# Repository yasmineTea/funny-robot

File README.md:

<h1>The Funny Exercise Robot</h1>

yo watup nino

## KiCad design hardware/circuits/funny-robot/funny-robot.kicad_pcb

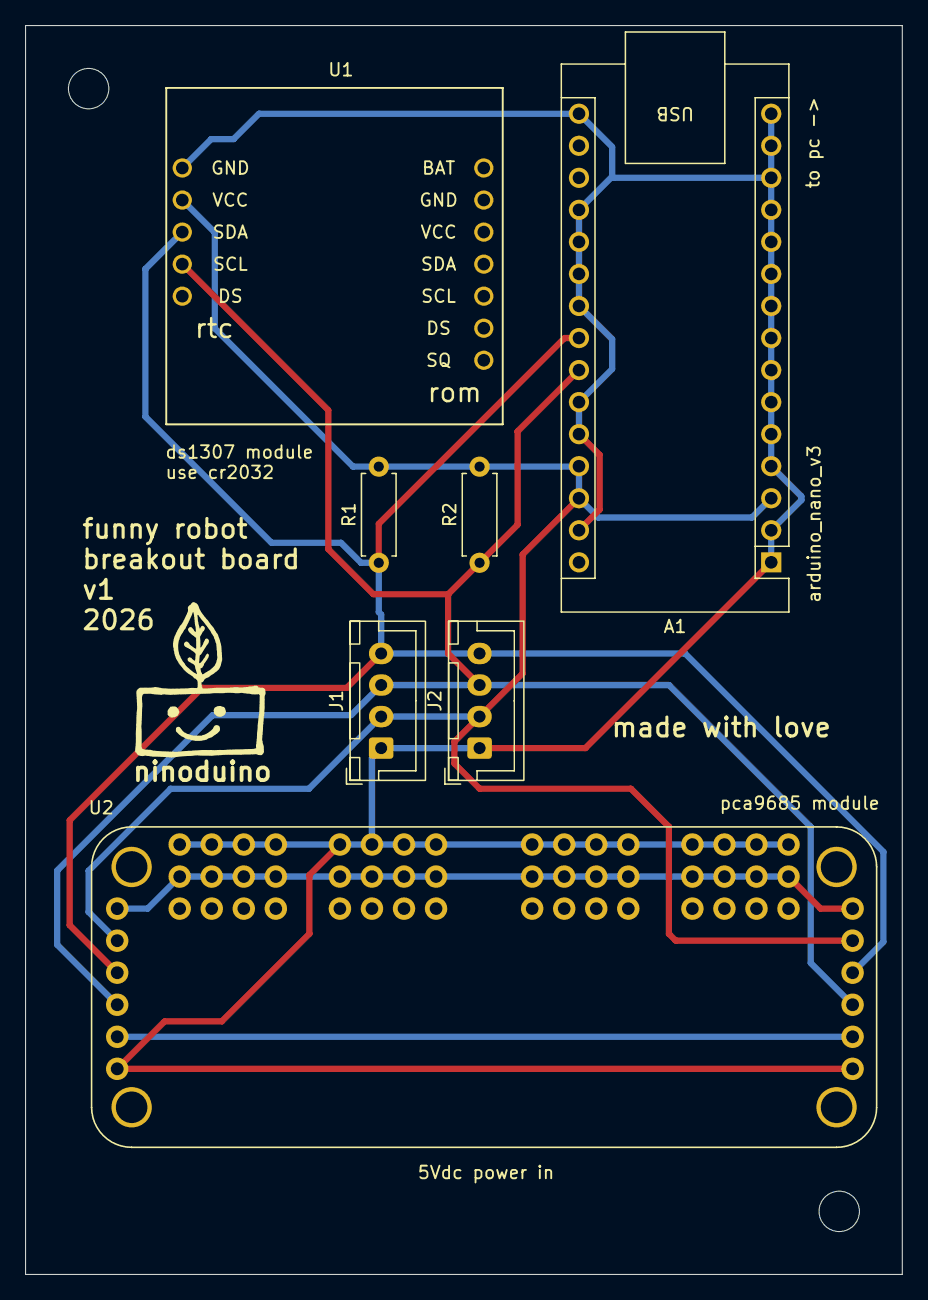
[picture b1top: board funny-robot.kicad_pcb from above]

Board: 2 copper layers, 69.5 x 99.0 mm, 7 parts (0 on the bottom side), 6 nets.

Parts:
A1: arduino_nano_v3; Arduino_Nano
J1: To SSD1306OLED; JST_XH_B4B-XH-A_1x04_P2.50mm_Vertical
J2: I2C Jumper; JST_XH_B4B-XH-A_1x04_P2.50mm_Vertical
R1, R2: 10k; R_Axial_DIN0207_L6.3mm_D2.5mm_P7.62mm_Horizontal
U1: Tiny_RTC_DS1307
U2: pca9685 module; MODULE_815

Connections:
+5V: U2.V+_1 (V+), U2.V+_2 (V+), U2.V+_3 (V+), U2.V+_4 (V+), U2.V+_5 (V+), U2.V+_6 (V+), U2.V+_7 (V+), U2.V+_8 (V+), U2.V+_9 (V+), U2.V+_10 (V+), U2.V+_11 (V+), U2.V+_12 (V+), U2.V+_13 (V+), U2.V+_14 (V+), U2.V+_15 (V+), U2.V+_16 (V+), U2.V+_17 (V+), U2.V+_18 (V+)
GND: A1.1 (D1/TX), A1.2 (D0/RX), A1.4 (GND), A1.5 (D2), A1.6 (D3), A1.7 (D4), A1.8 (D5), A1.9 (D6), A1.10 (D7), A1.11 (D8), A1.12 (D9), A1.13 (D10), A1.14 (D11), A1.15 (D12), A1.16 (D13), A1.19 (A0), A1.20 (A1), A1.21 (A2), A1.22 (A3), A1.25 (A6), A1.26 (A7), A1.29 (GND), J1.1, J2.1, U1.8 (GND), U2.GND_1 (GND), U2.GND_2 (GND), U2.GND_3 (GND), U2.GND_4 (GND), U2.GND_5 (GND), U2.GND_6 (GND), U2.GND_7 (GND), U2.GND_8 (GND), U2.GND_9 (GND), U2.GND_10 (GND), U2.GND_11 (GND), U2.GND_12 (GND), U2.GND_13 (GND), U2.GND_14 (GND), U2.GND_15 (GND), U2.GND_16 (GND), U2.GND_17 (GND), U2.GND_18 (GND)
unnamed: U2.OE_1 (~OE), U2.OE_2 (~OE)
SCL: A1.24 (A5), J1.3, J2.3, R2.1, U1.11 (SCL), U2.SCL_1 (SCL), U2.SCL_2 (SCL)
SDA: A1.23 (A4), J1.4, J2.4, R1.1, U1.10 (SDA), U2.SDA_1 (SDA), U2.SDA_2 (SDA)
VBUS: A1.3 (~RESET), A1.27 (+5V), A1.28 (~RESET), J1.2, J2.2, R1.2, R2.2, U1.9 (VCC), U2.VCC_1 (VCC), U2.VCC_2 (VCC)

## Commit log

2026-02-03 Create funnyRobot_arm_v2.f3d
    v2
2026-02-03 added 3d printing files
2026-02-06 Created schematic and pcb layout
2026-02-06 Adjusted logo font and text position
2026-02-10 created gerber files v1
2026-02-17 Updated PCB to comply with customs
2026-02-18 Elec Capst Microcontroller code, as of 02-17-2026
2026-03-03 organized ucontroller code
2026-04-05 added shoulders
2026-04-06 adjusted folders
2026-04-06 added arduino ino
2026-04-07 added rtc, servo com
2026-04-10 Added WPF
